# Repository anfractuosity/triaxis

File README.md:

# triaxis

3-axis RPi Pico based stepper driver, using TRINAMIC TMCSILENTSTEPSTICK SPI (TMC2130) modules.

Uses https://github.com/ncarandini/KiCad-RP-Pico for the Pico footprint.

## To Do

* Add 100+uF capacitor on 12V power rail below each driver, as datasheet mentions "A minimum capacity of 100µF near the driver is recommended for best performance"
* Larger 12V track width - see https://www.4pcb.com/trace-width-calculator.html
* Use thicker copper (2 oz)
* Finish software

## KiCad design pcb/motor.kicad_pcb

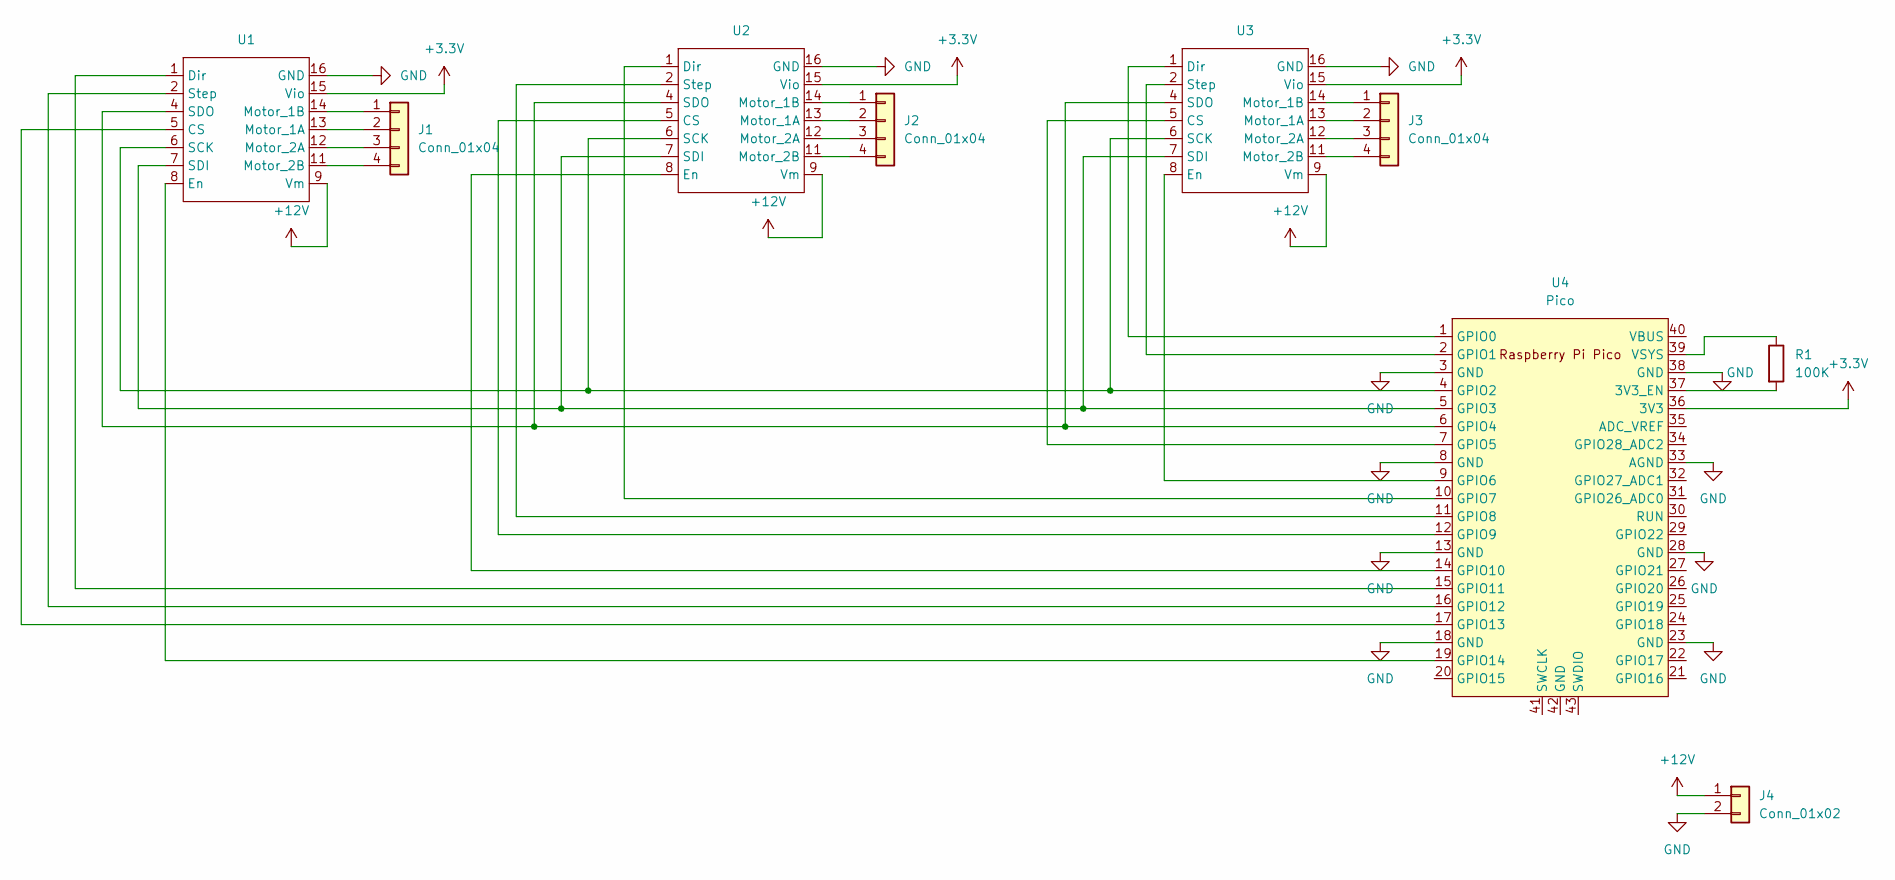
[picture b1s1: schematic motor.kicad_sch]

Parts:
J1, J2, J3: Conn_01x04; PinHeader_1x04_P2.54mm_Vertical
J4: Conn_01x02; PinHeader_1x02_P2.54mm_Vertical
R1: 100K; R_0805_2012Metric
U1, U2, U3: SILENTSTEPSTICK
U4: Pico; RPi_Pico_SMD_TH

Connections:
+3.3V: U1.15 (Vio), U2.15 (Vio), U3.15 (Vio), U4.36 (3V3)
+12V: J4.1, U1.9 (Vm), U2.9 (Vm), U3.9 (Vm)
GND: J4.2, U1.16 (GND), U2.16 (GND), U3.16 (GND), U4.3 (GND), U4.8 (GND), U4.13 (GND), U4.18 (GND), U4.23 (GND), U4.28 (GND), U4.33 (AGND), U4.38 (GND)
unnamed: J1.1, U1.14 (Motor_1B)
unnamed: J1.2, U1.13 (Motor_1A)
unnamed: J1.3, U1.12 (Motor_2A)
unnamed: J1.4, U1.11 (Motor_2B)
unnamed: J2.1, U2.14 (Motor_1B)
unnamed: J2.2, U2.13 (Motor_1A)
unnamed: J2.3, U2.12 (Motor_2A)
unnamed: J2.4, U2.11 (Motor_2B)
unnamed: J3.1, U3.14 (Motor_1B)
unnamed: J3.2, U3.13 (Motor_1A)
unnamed: J3.3, U3.12 (Motor_2A)
unnamed: J3.4, U3.11 (Motor_2B)
unnamed: U1.5 (CS), U4.17 (GPIO13)
unnamed: U1.1 (Dir), U4.15 (GPIO11)
unnamed: U1.8 (En), U4.19 (GPIO14)
unnamed: U1.6 (SCK), U2.6 (SCK), U3.6 (SCK), U4.4 (GPIO2)
unnamed: U1.7 (SDI), U2.7 (SDI), U3.7 (SDI), U4.5 (GPIO3)
unnamed: U1.4 (SDO), U2.4 (SDO), U3.4 (SDO), U4.6 (GPIO4)
unnamed: U1.2 (Step), U4.16 (GPIO12)
unnamed: U2.5 (CS), U4.12 (GPIO9)
unnamed: U2.1 (Dir), U4.10 (GPIO7)
unnamed: U2.8 (En), U4.14 (GPIO10)
unnamed: U2.2 (Step), U4.11 (GPIO8)
unnamed: U3.5 (CS), U4.7 (GPIO5)
unnamed: U3.1 (Dir), U4.1 (GPIO0)
unnamed: U3.8 (En), U4.9 (GPIO6)
unnamed: U3.2 (Step), U4.2 (GPIO1)
unnamed: R1.2, U4.37 (3V3_EN)
unnamed: R1.1, U4.39 (VSYS)

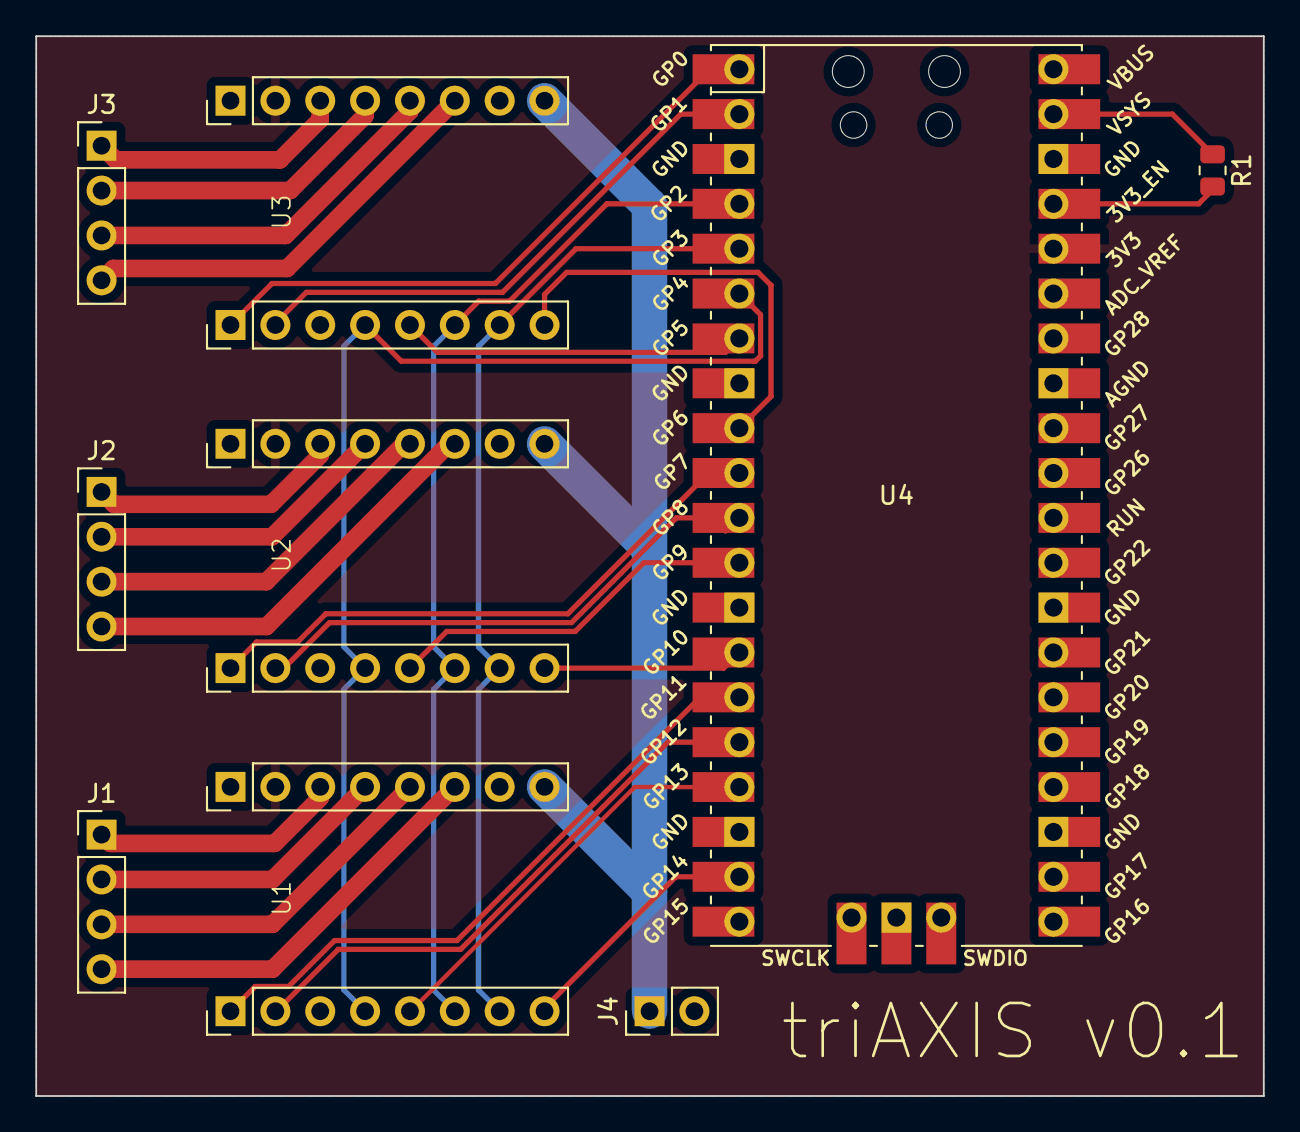
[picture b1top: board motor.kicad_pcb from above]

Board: 2 copper layers, 69.5 x 60.0 mm, 9 parts (0 on the bottom side), 32 nets.

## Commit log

2023-11-11 Change symbol name
2023-11-11 Readme
2023-11-12 To Do
